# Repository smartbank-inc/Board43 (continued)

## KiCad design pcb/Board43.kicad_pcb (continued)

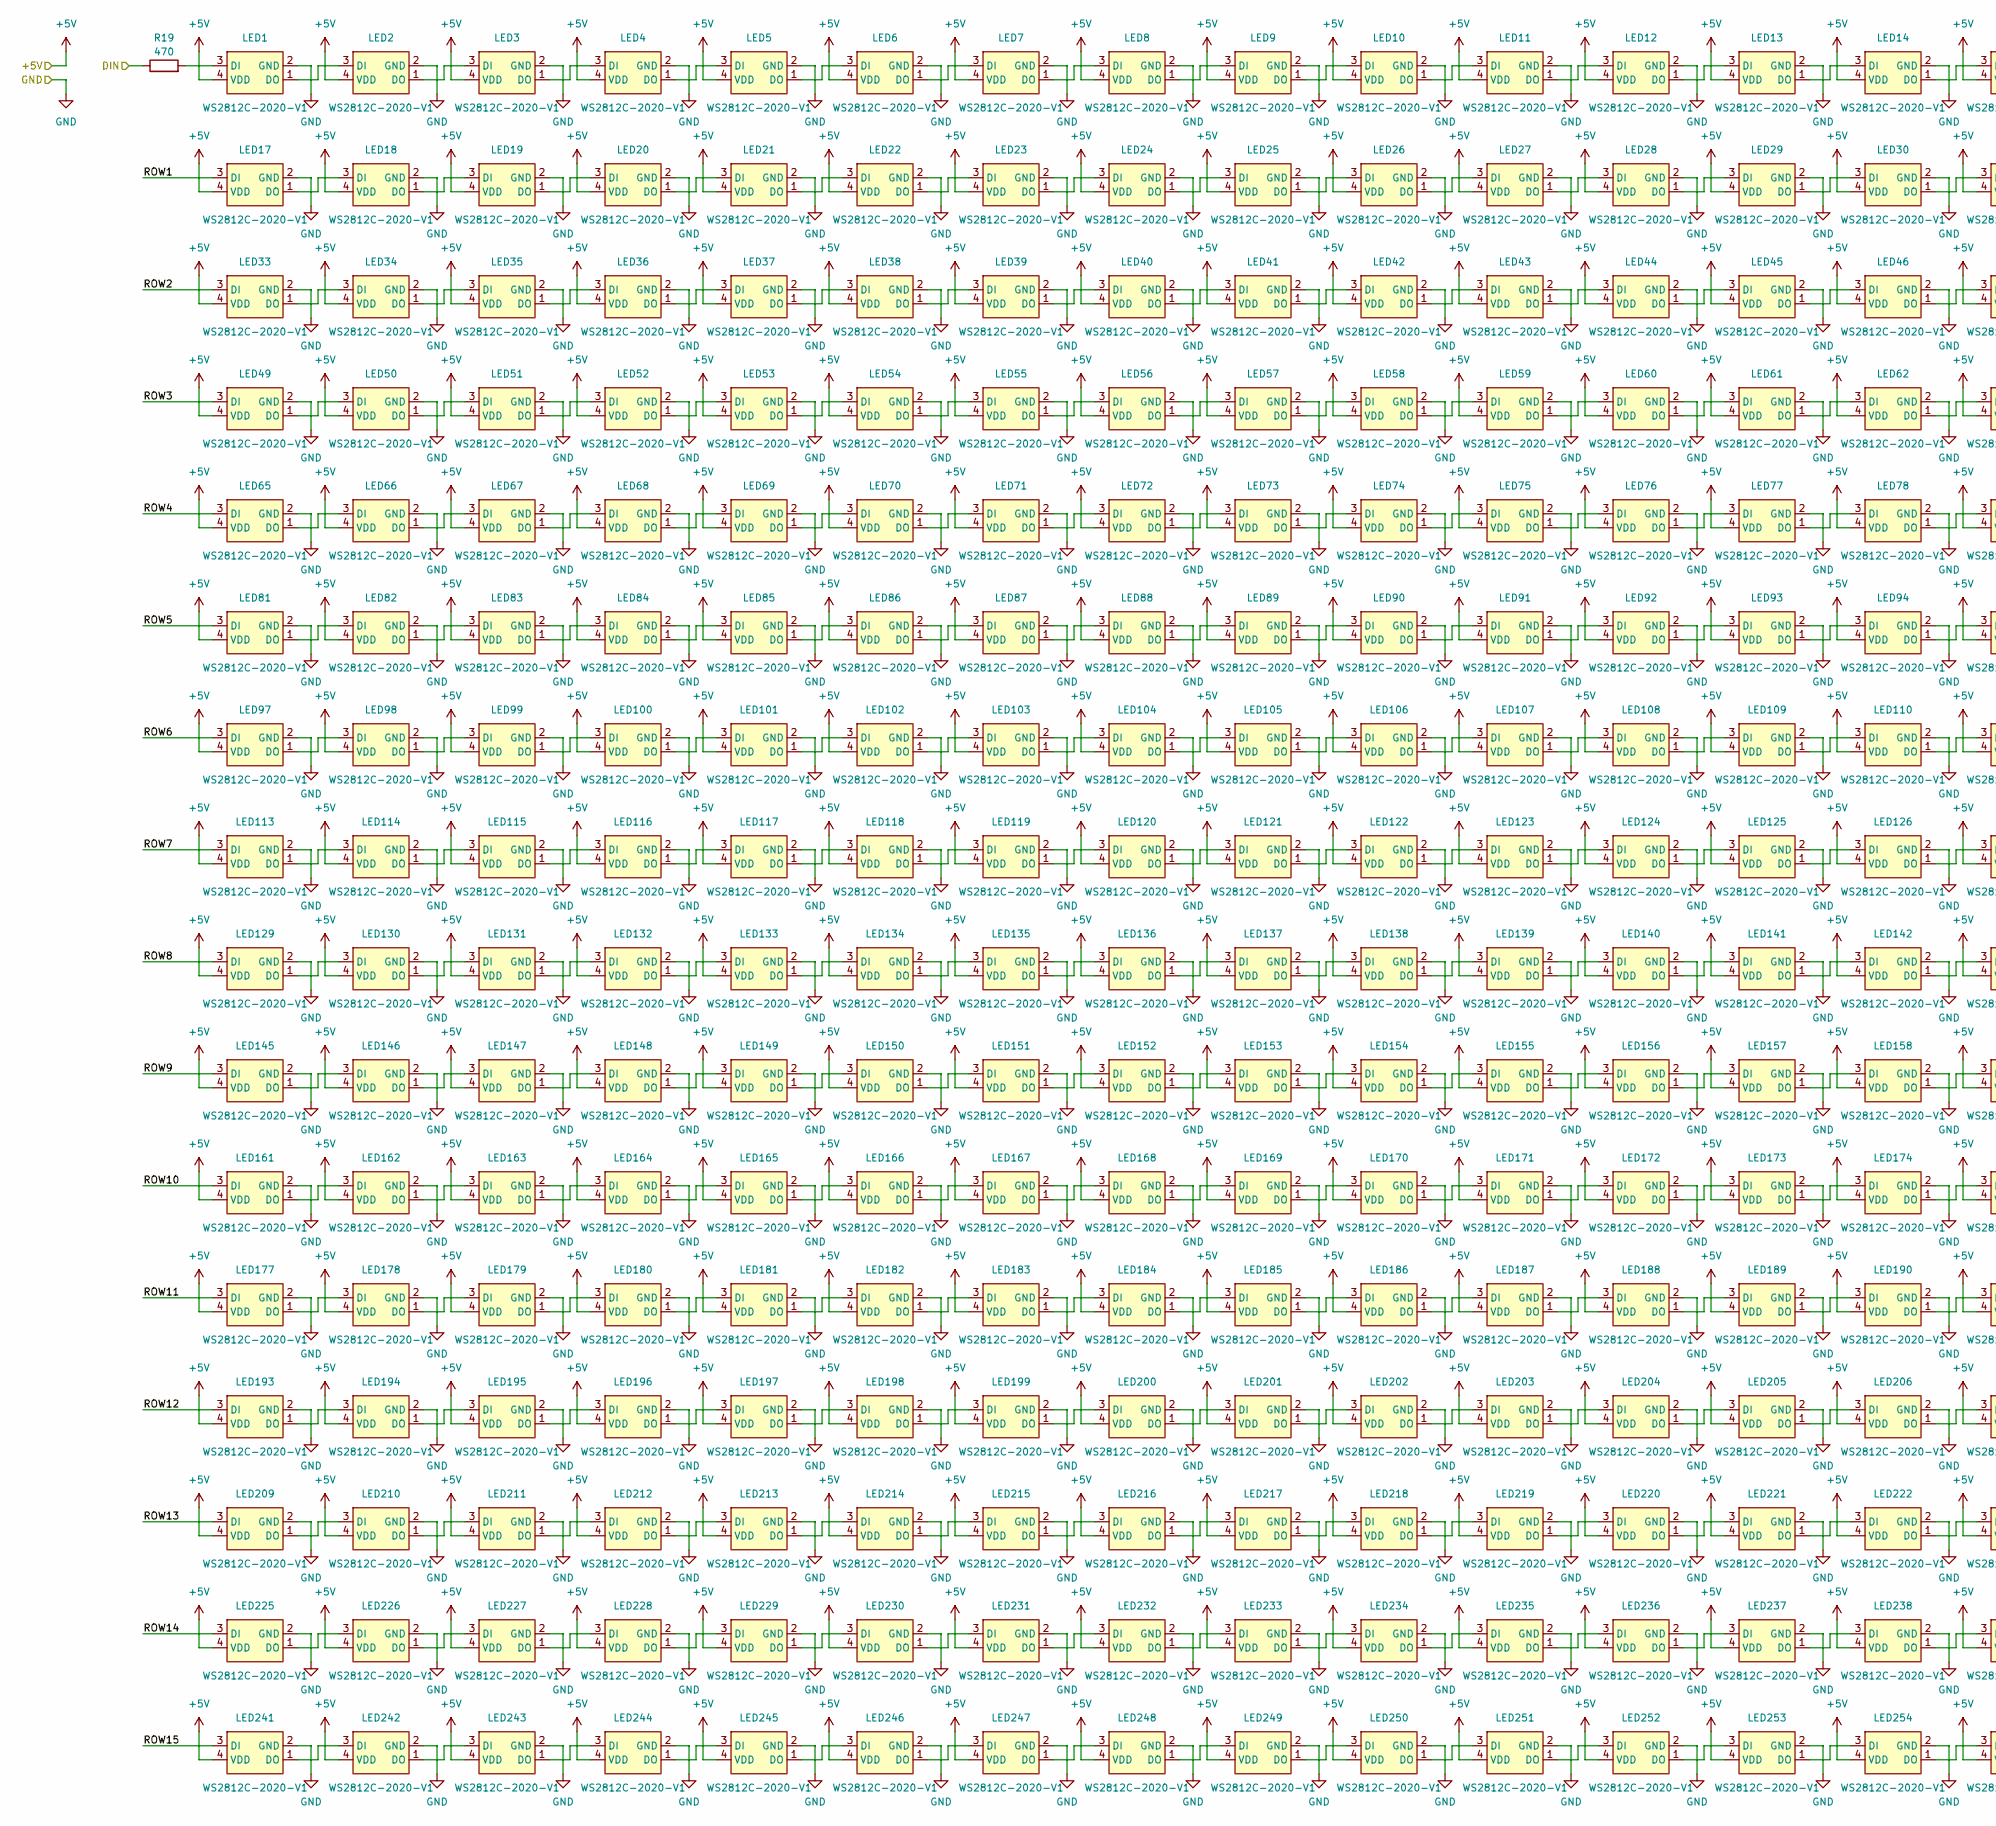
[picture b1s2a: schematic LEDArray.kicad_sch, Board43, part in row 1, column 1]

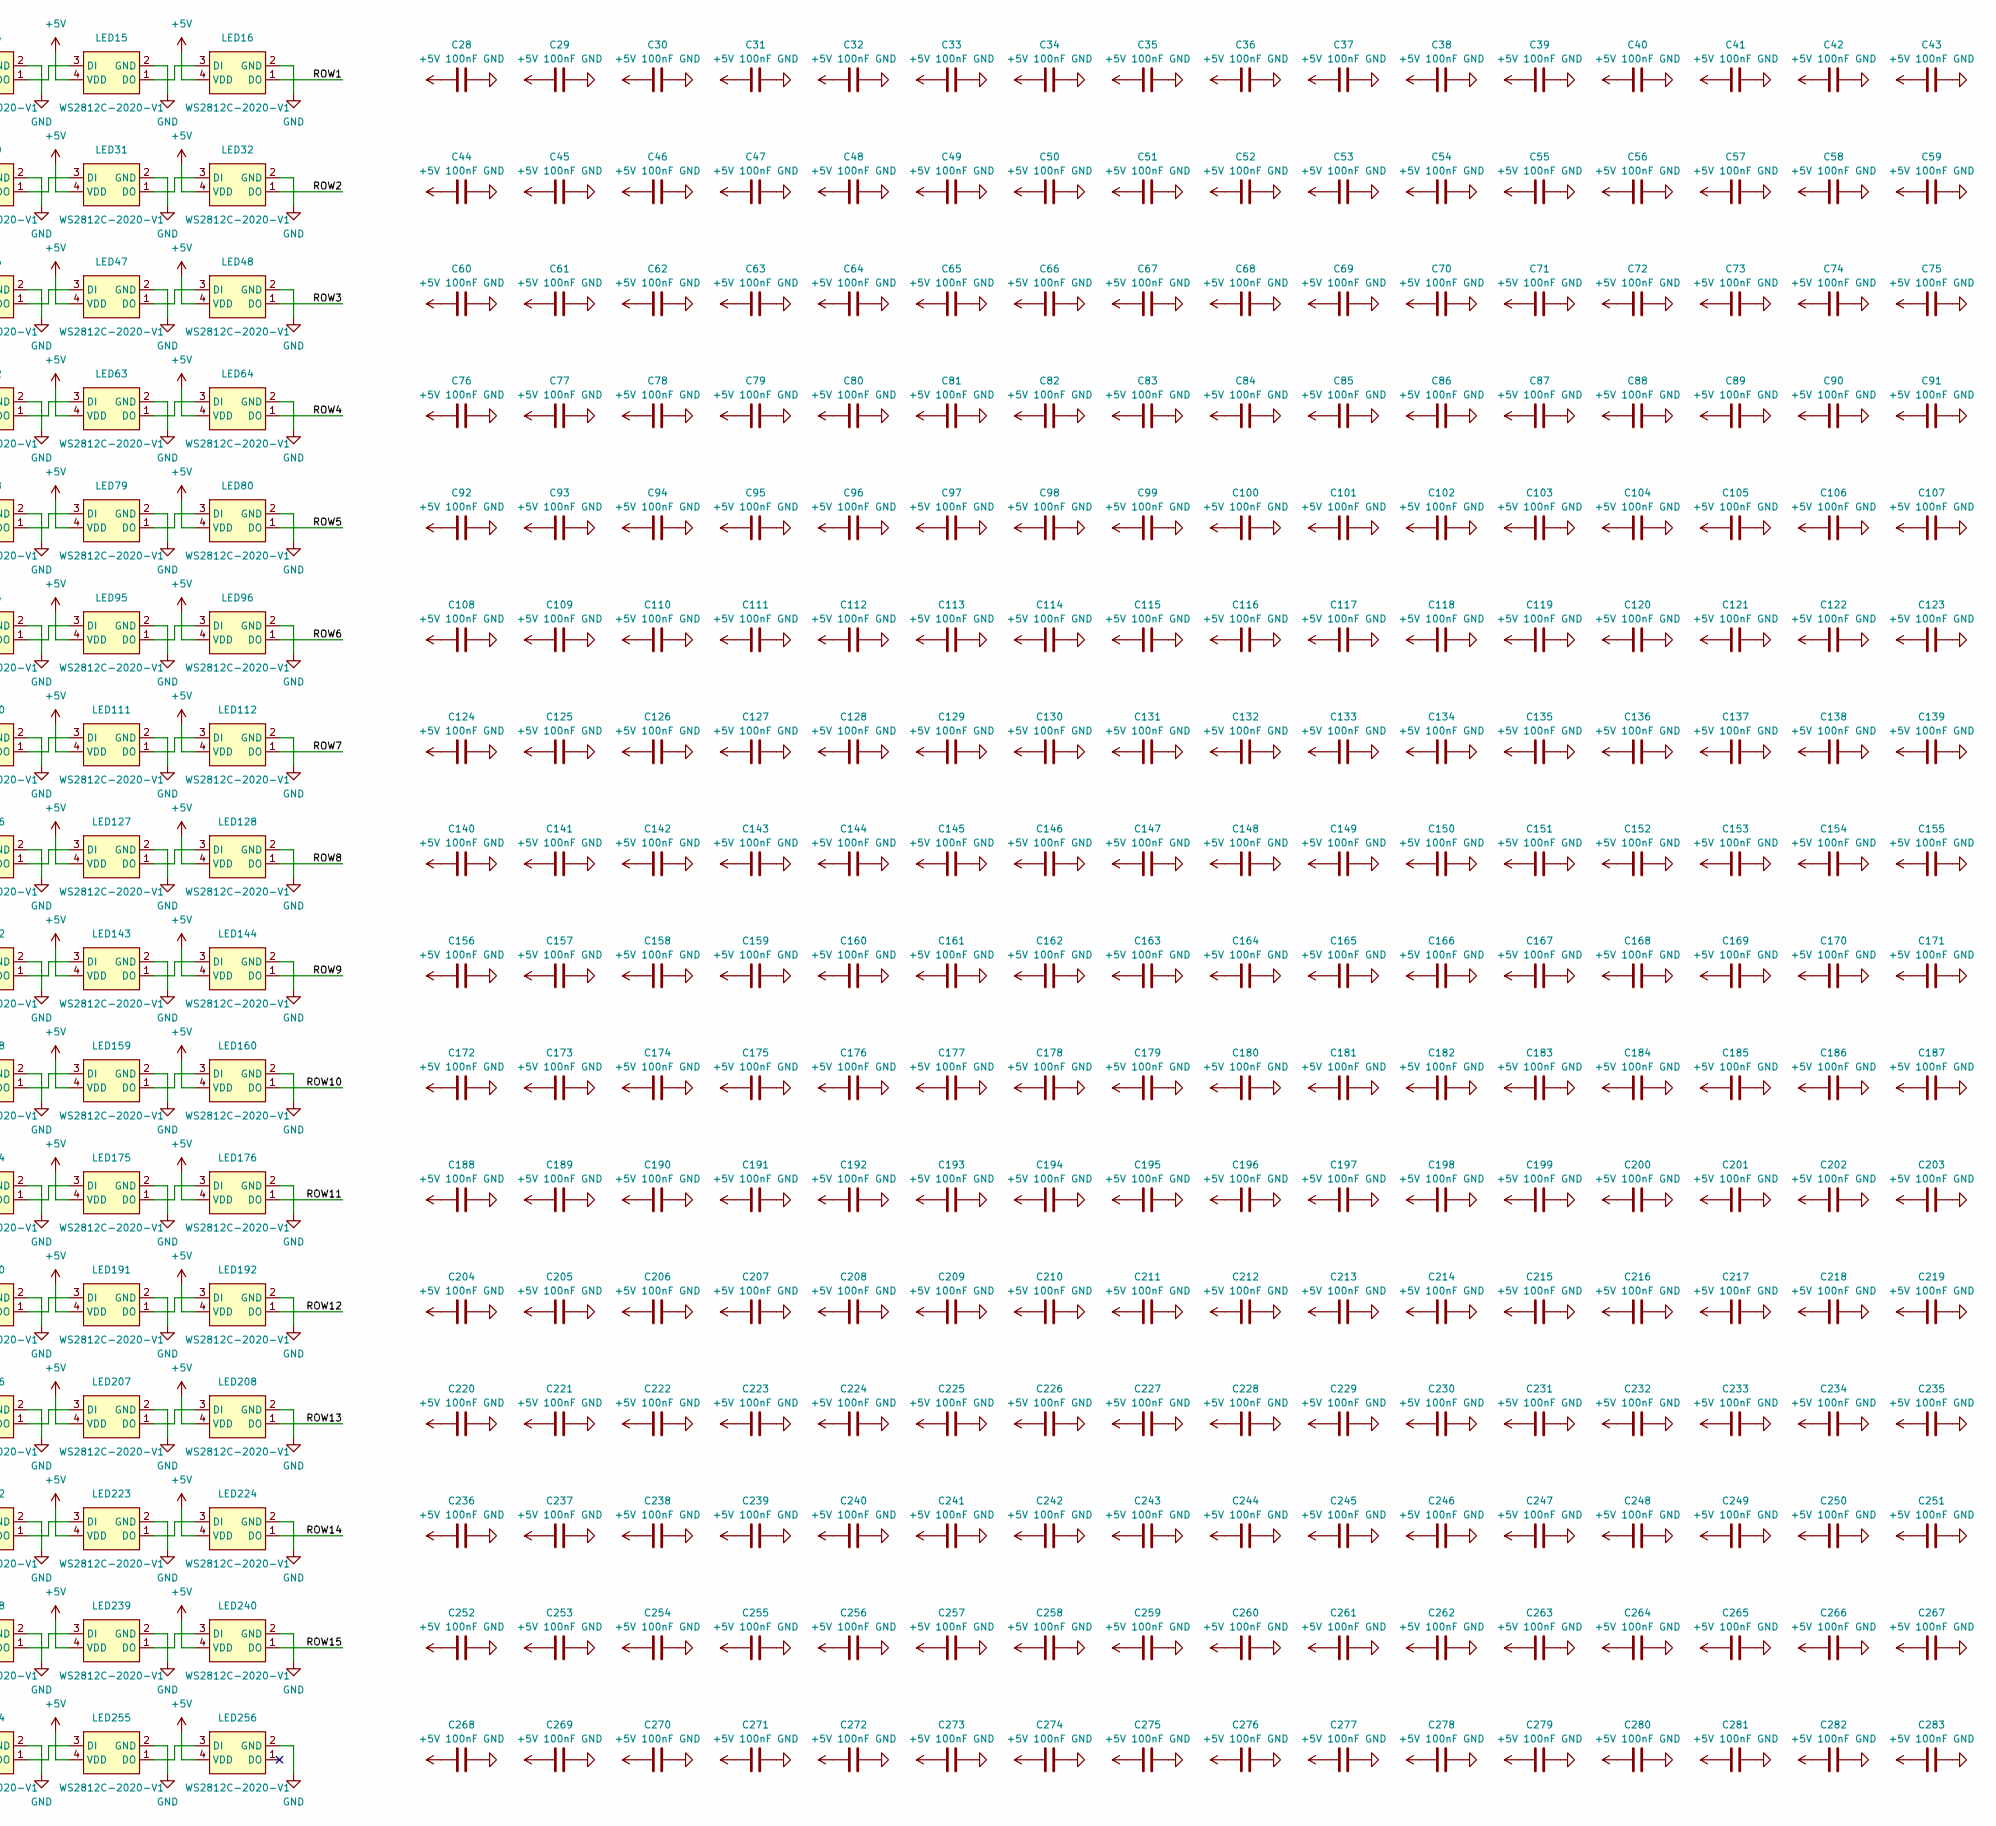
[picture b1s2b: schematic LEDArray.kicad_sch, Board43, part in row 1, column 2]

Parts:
C28, C29, C30, C31, C32, C33, C34, C35, C36, C37, C38, C39, C40, C41, C42, C43, C44, C45, C46, C47, C48, C49, C50, C51, C52, C53, C54, C55, C56, C57, C58, C59, C60, C61, C62, C63, C64, C65, C66, C67, C68, C69, C70, C71, C72, C73, C74, C75, C76, C77, C78, C79, C80, C81, C82, C83, C84, C85, C86, C87, C88, C89, C90, C91, C92, C93, C94, C95, C96, C97, C98, C99, C100, C101, C102, C103, C104, C105, C106, C107, C108, C109, C110, C111, C112, C113, C114, C115, C116, C117, C118, C119, C120, C121, C122, C123, C124, C125, C126, C127, C128, C129, C130, C131, C132, C133, C134, C135, C136, C137, C138, C139, C140, C141, C142, C143, C144, C145, C146, C147, C148, C149, C150, C151, C152, C153, C154, C155, C156, C157, C158, C159, C160, C161, C162, C163, C164, C165, C166, C167, C168, C169, C170, C171, C172, C173, C174, C175, C176, C177, C178, C179, C180, C181, C182, C183, C184, C185, C186, C187, C188, C189, C190, C191, C192, C193, C194, C195, C196, C197, C198, C199, C200, C201, C202, C203, C204, C205, C206, C207, C208, C209, C210, C211, C212, C213, C214, C215, C216, C217, C218, C219, C220, C221, C222, C223, C224, C225, C226, C227, C228, C229, C230, C231, C232, C233, C234, C235, C236, C237, C238, C239, C240, C241, C242, C243, C244, C245, C246, C247, C248, C249, C250, C251, C252, C253, C254, C255, C256, C257, C258, C259, C260, C261, C262, C263, C264, C265, C266, C267, C268, C269, C270, C271, C272, C273, C274, C275, C276, C277, C278, C279, C280, C281, C282, C283: 100nF; C_0201_0603Metric; LCSC C668346
LED1, LED2, LED3, LED4, LED5, LED6, LED7, LED8, LED9, LED10, LED11, LED12, LED13, LED14, LED15, LED16, LED17, LED18, LED19, LED20, LED21, LED22, LED23, LED24, LED25, LED26, LED27, LED28, LED29, LED30, LED31, LED32, LED33, LED34, LED35, LED36, LED37, LED38, LED39, LED40, LED41, LED42, LED43, LED44, LED45, LED46, LED47, LED48, LED49, LED50, LED51, LED52, LED53, LED54, LED55, LED56, LED57, LED58, LED59, LED60, LED61, LED62, LED63, LED64, LED65, LED66, LED67, LED68, LED69, LED70, LED71, LED72, LED73, LED74, LED75, LED76, LED77, LED78, LED79, LED80, LED81, LED82, LED83, LED84, LED85, LED86, LED87, LED88, LED89, LED90, LED91, LED92, LED93, LED94, LED95, LED96, LED97, LED98, LED99, LED100, LED101, LED102, LED103, LED104, LED105, LED106, LED107, LED108, LED109, LED110, LED111, LED112, LED113, LED114, LED115, LED116, LED117, LED118, LED119, LED120, LED121, LED122, LED123, LED124, LED125, LED126, LED127, LED128, LED129, LED130, LED131, LED132, LED133, LED134, LED135, LED136, LED137, LED138, LED139, LED140, LED141, LED142, LED143, LED144, LED145, LED146, LED147, LED148, LED149, LED150, LED151, LED152, LED153, LED154, LED155, LED156, LED157, LED158, LED159, LED160, LED161, LED162, LED163, LED164, LED165, LED166, LED167, LED168, LED169, LED170, LED171, LED172, LED173, LED174, LED175, LED176, LED177, LED178, LED179, LED180, LED181, LED182, LED183, LED184, LED185, LED186, LED187, LED188, LED189, LED190, LED191, LED192, LED193, LED194, LED195, LED196, LED197, LED198, LED199, LED200, LED201, LED202, LED203, LED204, LED205, LED206, LED207, LED208, LED209, LED210, LED211, LED212, LED213, LED214, LED215, LED216, LED217, LED218, LED219, LED220, LED221, LED222, LED223, LED224, LED225, LED226, LED227, LED228, LED229, LED230, LED231, LED232, LED233, LED234, LED235, LED236, LED237, LED238, LED239, LED240, LED241, LED242, LED243, LED244, LED245, LED246, LED247, LED248, LED249, LED250, LED251, LED252, LED253, LED254, LED255, LED256: WS2812C-2020-V1; LCSC C2976072
R19: 470; R_0201_0603Metric; LCSC C473464

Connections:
+5V: C28.1, C29.1, C30.1, C31.1, C32.1, C33.1, C34.1, C35.1, C36.1, C37.1, C38.1, C39.1, C40.1, C41.1, C42.1, C43.1, C44.1, C45.1, C46.1, C47.1, C48.1, C49.1, C50.1, C51.1, C52.1, C53.1, C54.1, C55.1, C56.1, C57.1, C58.1, C59.1, C60.1, C61.1, C62.1, C63.1, C64.1, C65.1, C66.1, C67.1, C68.1, C69.1, C70.1, C71.1, C72.1, C73.1, C74.1, C75.1, C76.1, C77.1, C78.1, C79.1, C80.1, C81.1, C82.1, C83.1, C84.1, C85.1, C86.1, C87.1, C88.1, C89.1, C90.1, C91.1, C92.1, C93.1, C94.1, C95.1, C96.1, C97.1, C98.1, C99.1, C100.1, C101.1, C102.1, C103.1, C104.1, C105.1, C106.1, C107.1, C108.1, C109.1, C110.1, C111.1, C112.1, C113.1, C114.1, C115.1, C116.1, C117.1, C118.1, C119.1, C120.1, C121.1, C122.1, C123.1, C124.1, C125.1, C126.1, C127.1, C128.1, C129.1, C130.1, C131.1, C132.1, C133.1, C134.1, C135.1, C136.1, C137.1, C138.1, C139.1, C140.1, C141.1, C142.1, C143.1, C144.1, C145.1, C146.1, C147.1, C148.1, C149.1, C150.1, C151.1, C152.1, C153.1, C154.1, C155.1, C156.1, C157.1, C158.1, C159.1, C160.1, C161.1, C162.1, C163.1, C164.1, C165.1, C166.1, C167.1, C168.1, C169.1, C170.1, C171.1, C172.1, C173.1, C174.1, C175.1, C176.1, C177.1, C178.1, C179.1, C180.1, C181.1, C182.1, C183.1, C184.1, C185.1, C186.1, C187.1, C188.1, C189.1, C190.1, C191.1, C192.1, C193.1, C194.1, C195.1, C196.1, C197.1, C198.1, C199.1, C200.1, C201.1, C202.1, C203.1, C204.1, C205.1, C206.1, C207.1, C208.1, C209.1, C210.1, C211.1, C212.1, C213.1, C214.1, C215.1, C216.1, C217.1, C218.1, C219.1, C220.1, C221.1, C222.1, C223.1, C224.1, C225.1, C226.1, C227.1, C228.1, C229.1, C230.1, C231.1, C232.1, C233.1, C234.1, C235.1, C236.1, C237.1, C238.1, C239.1, C240.1, C241.1, C242.1, C243.1, C244.1, C245.1, C246.1, C247.1, C248.1, C249.1, C250.1, C251.1, C252.1, C253.1, C254.1, C255.1, C256.1, C257.1, C258.1, C259.1, C260.1, C261.1, C262.1, C263.1, C264.1, C265.1, C266.1, C267.1, C268.1, C269.1, C270.1, C271.1, C272.1, C273.1, C274.1, C275.1, C276.1, C277.1, C278.1, C279.1, C280.1, C281.1, C282.1, C283.1, LED1.4 (VDD), LED2.4 (VDD), LED3.4 (VDD), LED4.4 (VDD), LED5.4 (VDD), LED6.4 (VDD), LED7.4 (VDD), LED8.4 (VDD), LED9.4 (VDD), LED10.4 (VDD), LED11.4 (VDD), LED12.4 (VDD), LED13.4 (VDD), LED14.4 (VDD), LED15.4 (VDD), LED16.4 (VDD), LED17.4 (VDD), LED18.4 (VDD), LED19.4 (VDD), LED20.4 (VDD), LED21.4 (VDD), LED22.4 (VDD), LED23.4 (VDD), LED24.4 (VDD), LED25.4 (VDD), LED26.4 (VDD), LED27.4 (VDD), LED28.4 (VDD), LED29.4 (VDD), LED30.4 (VDD), LED31.4 (VDD), LED32.4 (VDD), LED33.4 (VDD), LED34.4 (VDD), LED35.4 (VDD), LED36.4 (VDD), LED37.4 (VDD), LED38.4 (VDD), LED39.4 (VDD), LED40.4 (VDD), LED41.4 (VDD), LED42.4 (VDD), LED43.4 (VDD), LED44.4 (VDD), LED45.4 (VDD), LED46.4 (VDD), LED47.4 (VDD), LED48.4 (VDD), LED49.4 (VDD), LED50.4 (VDD), LED51.4 (VDD), LED52.4 (VDD), LED53.4 (VDD), LED54.4 (VDD), LED55.4 (VDD), LED56.4 (VDD), LED57.4 (VDD), LED58.4 (VDD), LED59.4 (VDD), LED60.4 (VDD), LED61.4 (VDD), LED62.4 (VDD), LED63.4 (VDD), LED64.4 (VDD), LED65.4 (VDD), LED66.4 (VDD), LED67.4 (VDD), LED68.4 (VDD), LED69.4 (VDD), LED70.4 (VDD), LED71.4 (VDD), LED72.4 (VDD), LED73.4 (VDD), LED74.4 (VDD), LED75.4 (VDD), LED76.4 (VDD), LED77.4 (VDD), LED78.4 (VDD), LED79.4 (VDD), LED80.4 (VDD), LED81.4 (VDD), LED82.4 (VDD), LED83.4 (VDD), LED84.4 (VDD), LED85.4 (VDD), LED86.4 (VDD), LED87.4 (VDD), LED88.4 (VDD), LED89.4 (VDD), LED90.4 (VDD), LED91.4 (VDD), LED92.4 (VDD), LED93.4 (VDD), LED94.4 (VDD), LED95.4 (VDD), LED96.4 (VDD), LED97.4 (VDD), LED98.4 (VDD), LED99.4 (VDD), LED100.4 (VDD), LED101.4 (VDD), LED102.4 (VDD), LED103.4 (VDD), LED104.4 (VDD), LED105.4 (VDD), LED106.4 (VDD), LED107.4 (VDD), LED108.4 (VDD), LED109.4 (VDD), LED110.4 (VDD), LED111.4 (VDD), LED112.4 (VDD), LED113.4 (VDD), LED114.4 (VDD), LED115.4 (VDD), LED116.4 (VDD), LED117.4 (VDD), LED118.4 (VDD), LED119.4 (VDD), LED120.4 (VDD), LED121.4 (VDD), LED122.4 (VDD), LED123.4 (VDD), LED124.4 (VDD), LED125.4 (VDD), LED126.4 (VDD), LED127.4 (VDD), LED128.4 (VDD), LED129.4 (VDD), LED130.4 (VDD), LED131.4 (VDD), LED132.4 (VDD), LED133.4 (VDD), LED134.4 (VDD), LED135.4 (VDD), LED136.4 (VDD), LED137.4 (VDD), LED138.4 (VDD), LED139.4 (VDD), LED140.4 (VDD), LED141.4 (VDD), LED142.4 (VDD), LED143.4 (VDD), LED144.4 (VDD), LED145.4 (VDD), LED146.4 (VDD), LED147.4 (VDD), LED148.4 (VDD), LED149.4 (VDD), LED150.4 (VDD), LED151.4 (VDD), LED152.4 (VDD), LED153.4 (VDD), LED154.4 (VDD), LED155.4 (VDD), LED156.4 (VDD), LED157.4 (VDD), LED158.4 (VDD), LED159.4 (VDD), LED160.4 (VDD), LED161.4 (VDD), LED162.4 (VDD), LED163.4 (VDD), LED164.4 (VDD), LED165.4 (VDD), LED166.4 (VDD), LED167.4 (VDD), LED168.4 (VDD), LED169.4 (VDD), LED170.4 (VDD), LED171.4 (VDD), LED172.4 (VDD), LED173.4 (VDD), LED174.4 (VDD), LED175.4 (VDD), LED176.4 (VDD), LED177.4 (VDD), LED178.4 (VDD), LED179.4 (VDD), LED180.4 (VDD), LED181.4 (VDD), LED182.4 (VDD), LED183.4 (VDD), LED184.4 (VDD), LED185.4 (VDD), LED186.4 (VDD), LED187.4 (VDD), LED188.4 (VDD), LED189.4 (VDD), LED190.4 (VDD), LED191.4 (VDD), LED192.4 (VDD), LED193.4 (VDD), LED194.4 (VDD), LED195.4 (VDD), LED196.4 (VDD), LED197.4 (VDD), LED198.4 (VDD), LED199.4 (VDD), LED200.4 (VDD), LED201.4 (VDD), LED202.4 (VDD), LED203.4 (VDD), LED204.4 (VDD), LED205.4 (VDD), LED206.4 (VDD), LED207.4 (VDD), LED208.4 (VDD), LED209.4 (VDD), LED210.4 (VDD), LED211.4 (VDD), LED212.4 (VDD), LED213.4 (VDD), LED214.4 (VDD), LED215.4 (VDD), LED216.4 (VDD), LED217.4 (VDD), LED218.4 (VDD), LED219.4 (VDD), LED220.4 (VDD), LED221.4 (VDD), LED222.4 (VDD), LED223.4 (VDD), LED224.4 (VDD), LED225.4 (VDD), LED226.4 (VDD), LED227.4 (VDD), LED228.4 (VDD), LED229.4 (VDD), LED230.4 (VDD), LED231.4 (VDD), LED232.4 (VDD), LED233.4 (VDD), LED234.4 (VDD), LED235.4 (VDD), LED236.4 (VDD), LED237.4 (VDD), LED238.4 (VDD), LED239.4 (VDD), LED240.4 (VDD), LED241.4 (VDD), LED242.4 (VDD), LED243.4 (VDD), LED244.4 (VDD), LED245.4 (VDD), LED246.4 (VDD), LED247.4 (VDD), LED248.4 (VDD), LED249.4 (VDD), LED250.4 (VDD), LED251.4 (VDD), LED252.4 (VDD), LED253.4 (VDD), LED254.4 (VDD), LED255.4 (VDD), LED256.4 (VDD); also elsewhere on the board
/LED OUT: R19.1; also elsewhere on the board
/LEDArray/ROW1: LED16.1 (DO), LED17.3 (DI)
/LEDArray/ROW2: LED32.1 (DO), LED33.3 (DI)
/LEDArray/ROW3: LED48.1 (DO), LED49.3 (DI)
/LEDArray/ROW4: LED64.1 (DO), LED65.3 (DI)
/LEDArray/ROW5: LED80.1 (DO), LED81.3 (DI)
/LEDArray/ROW6: LED96.1 (DO), LED97.3 (DI)
/LEDArray/ROW7: LED112.1 (DO), LED113.3 (DI)
/LEDArray/ROW8: LED128.1 (DO), LED129.3 (DI)
/LEDArray/ROW9: LED144.1 (DO), LED145.3 (DI)
/LEDArray/ROW10: LED160.1 (DO), LED161.3 (DI)
/LEDArray/ROW11: LED176.1 (DO), LED177.3 (DI)
/LEDArray/ROW12: LED192.1 (DO), LED193.3 (DI)
/LEDArray/ROW13: LED208.1 (DO), LED209.3 (DI)
/LEDArray/ROW14: LED224.1 (DO), LED225.3 (DI)
/LEDArray/ROW15: LED240.1 (DO), LED241.3 (DI)
GND: C28.2, C29.2, C30.2, C31.2, C32.2, C33.2, C34.2, C35.2, C36.2, C37.2, C38.2, C39.2, C40.2, C41.2, C42.2, C43.2, C44.2, C45.2, C46.2, C47.2, C48.2, C49.2, C50.2, C51.2, C52.2, C53.2, C54.2, C55.2, C56.2, C57.2, C58.2, C59.2, C60.2, C61.2, C62.2, C63.2, C64.2, C65.2, C66.2, C67.2, C68.2, C69.2, C70.2, C71.2, C72.2, C73.2, C74.2, C75.2, C76.2, C77.2, C78.2, C79.2, C80.2, C81.2, C82.2, C83.2, C84.2, C85.2, C86.2, C87.2, C88.2, C89.2, C90.2, C91.2, C92.2, C93.2, C94.2, C95.2, C96.2, C97.2, C98.2, C99.2, C100.2, C101.2, C102.2, C103.2, C104.2, C105.2, C106.2, C107.2, C108.2, C109.2, C110.2, C111.2, C112.2, C113.2, C114.2, C115.2, C116.2, C117.2, C118.2, C119.2, C120.2, C121.2, C122.2, C123.2, C124.2, C125.2, C126.2, C127.2, C128.2, C129.2, C130.2, C131.2, C132.2, C133.2, C134.2, C135.2, C136.2, C137.2, C138.2, C139.2, C140.2, C141.2, C142.2, C143.2, C144.2, C145.2, C146.2, C147.2, C148.2, C149.2, C150.2, C151.2, C152.2, C153.2, C154.2, C155.2, C156.2, C157.2, C158.2, C159.2, C160.2, C161.2, C162.2, C163.2, C164.2, C165.2, C166.2, C167.2, C168.2, C169.2, C170.2, C171.2, C172.2, C173.2, C174.2, C175.2, C176.2, C177.2, C178.2, C179.2, C180.2, C181.2, C182.2, C183.2, C184.2, C185.2, C186.2, C187.2, C188.2, C189.2, C190.2, C191.2, C192.2, C193.2, C194.2, C195.2, C196.2, C197.2, C198.2, C199.2, C200.2, C201.2, C202.2, C203.2, C204.2, C205.2, C206.2, C207.2, C208.2, C209.2, C210.2, C211.2, C212.2, C213.2, C214.2, C215.2, C216.2, C217.2, C218.2, C219.2, C220.2, C221.2, C222.2, C223.2, C224.2, C225.2, C226.2, C227.2, C228.2, C229.2, C230.2, C231.2, C232.2, C233.2, C234.2, C235.2, C236.2, C237.2, C238.2, C239.2, C240.2, C241.2, C242.2, C243.2, C244.2, C245.2, C246.2, C247.2, C248.2, C249.2, C250.2, C251.2, C252.2, C253.2, C254.2, C255.2, C256.2, C257.2, C258.2, C259.2, C260.2, C261.2, C262.2, C263.2, C264.2, C265.2, C266.2, C267.2, C268.2, C269.2, C270.2, C271.2, C272.2, C273.2, C274.2, C275.2, C276.2, C277.2, C278.2, C279.2, C280.2, C281.2, C282.2, C283.2, LED1.2 (GND), LED2.2 (GND), LED3.2 (GND), LED4.2 (GND), LED5.2 (GND), LED6.2 (GND), LED7.2 (GND), LED8.2 (GND), LED9.2 (GND), LED10.2 (GND), LED11.2 (GND), LED12.2 (GND), LED13.2 (GND), LED14.2 (GND), LED15.2 (GND), LED16.2 (GND), LED17.2 (GND), LED18.2 (GND), LED19.2 (GND), LED20.2 (GND), LED21.2 (GND), LED22.2 (GND), LED23.2 (GND), LED24.2 (GND), LED25.2 (GND), LED26.2 (GND), LED27.2 (GND), LED28.2 (GND), LED29.2 (GND), LED30.2 (GND), LED31.2 (GND), LED32.2 (GND), LED33.2 (GND), LED34.2 (GND), LED35.2 (GND), LED36.2 (GND), LED37.2 (GND), LED38.2 (GND), LED39.2 (GND), LED40.2 (GND), LED41.2 (GND), LED42.2 (GND), LED43.2 (GND), LED44.2 (GND), LED45.2 (GND), LED46.2 (GND), LED47.2 (GND), LED48.2 (GND), LED49.2 (GND), LED50.2 (GND), LED51.2 (GND), LED52.2 (GND), LED53.2 (GND), LED54.2 (GND), LED55.2 (GND), LED56.2 (GND), LED57.2 (GND), LED58.2 (GND), LED59.2 (GND), LED60.2 (GND), LED61.2 (GND), LED62.2 (GND), LED63.2 (GND), LED64.2 (GND), LED65.2 (GND), LED66.2 (GND), LED67.2 (GND), LED68.2 (GND), LED69.2 (GND), LED70.2 (GND), LED71.2 (GND), LED72.2 (GND), LED73.2 (GND), LED74.2 (GND), LED75.2 (GND), LED76.2 (GND), LED77.2 (GND), LED78.2 (GND), LED79.2 (GND), LED80.2 (GND), LED81.2 (GND), LED82.2 (GND), LED83.2 (GND), LED84.2 (GND), LED85.2 (GND), LED86.2 (GND), LED87.2 (GND), LED88.2 (GND), LED89.2 (GND), LED90.2 (GND), LED91.2 (GND), LED92.2 (GND), LED93.2 (GND), LED94.2 (GND), LED95.2 (GND), LED96.2 (GND), LED97.2 (GND), LED98.2 (GND), LED99.2 (GND), LED100.2 (GND), LED101.2 (GND), LED102.2 (GND), LED103.2 (GND), LED104.2 (GND), LED105.2 (GND), LED106.2 (GND), LED107.2 (GND), LED108.2 (GND), LED109.2 (GND), LED110.2 (GND), LED111.2 (GND), LED112.2 (GND), LED113.2 (GND), LED114.2 (GND), LED115.2 (GND), LED116.2 (GND), LED117.2 (GND), LED118.2 (GND), LED119.2 (GND), LED120.2 (GND), LED121.2 (GND), LED122.2 (GND), LED123.2 (GND), LED124.2 (GND), LED125.2 (GND), LED126.2 (GND), LED127.2 (GND), LED128.2 (GND), LED129.2 (GND), LED130.2 (GND), LED131.2 (GND), LED132.2 (GND), LED133.2 (GND), LED134.2 (GND), LED135.2 (GND), LED136.2 (GND), LED137.2 (GND), LED138.2 (GND), LED139.2 (GND), LED140.2 (GND), LED141.2 (GND), LED142.2 (GND), LED143.2 (GND), LED144.2 (GND), LED145.2 (GND), LED146.2 (GND), LED147.2 (GND), LED148.2 (GND), LED149.2 (GND), LED150.2 (GND), LED151.2 (GND), LED152.2 (GND), LED153.2 (GND), LED154.2 (GND), LED155.2 (GND), LED156.2 (GND), LED157.2 (GND), LED158.2 (GND), LED159.2 (GND), LED160.2 (GND), LED161.2 (GND), LED162.2 (GND), LED163.2 (GND), LED164.2 (GND), LED165.2 (GND), LED166.2 (GND), LED167.2 (GND), LED168.2 (GND), LED169.2 (GND), LED170.2 (GND), LED171.2 (GND), LED172.2 (GND), LED173.2 (GND), LED174.2 (GND), LED175.2 (GND), LED176.2 (GND), LED177.2 (GND), LED178.2 (GND), LED179.2 (GND), LED180.2 (GND), LED181.2 (GND), LED182.2 (GND), LED183.2 (GND), LED184.2 (GND), LED185.2 (GND), LED186.2 (GND), LED187.2 (GND), LED188.2 (GND), LED189.2 (GND), LED190.2 (GND), LED191.2 (GND), LED192.2 (GND), LED193.2 (GND), LED194.2 (GND), LED195.2 (GND), LED196.2 (GND), LED197.2 (GND), LED198.2 (GND), LED199.2 (GND), LED200.2 (GND), LED201.2 (GND), LED202.2 (GND), LED203.2 (GND), LED204.2 (GND), LED205.2 (GND), LED206.2 (GND), LED207.2 (GND), LED208.2 (GND), LED209.2 (GND), LED210.2 (GND), LED211.2 (GND), LED212.2 (GND), LED213.2 (GND), LED214.2 (GND), LED215.2 (GND), LED216.2 (GND), LED217.2 (GND), LED218.2 (GND), LED219.2 (GND), LED220.2 (GND), LED221.2 (GND), LED222.2 (GND), LED223.2 (GND), LED224.2 (GND), LED225.2 (GND), LED226.2 (GND), LED227.2 (GND), LED228.2 (GND), LED229.2 (GND), LED230.2 (GND), LED231.2 (GND), LED232.2 (GND), LED233.2 (GND), LED234.2 (GND), LED235.2 (GND), LED236.2 (GND), LED237.2 (GND), LED238.2 (GND), LED239.2 (GND), LED240.2 (GND), LED241.2 (GND), LED242.2 (GND), LED243.2 (GND), LED244.2 (GND), LED245.2 (GND), LED246.2 (GND), LED247.2 (GND), LED248.2 (GND), LED249.2 (GND), LED250.2 (GND), LED251.2 (GND), LED252.2 (GND), LED253.2 (GND), LED254.2 (GND), LED255.2 (GND), LED256.2 (GND); also elsewhere on the board
unnamed: LED1.3 (DI), R19.2
unnamed: LED1.1 (DO), LED2.3 (DI)
unnamed: LED2.1 (DO), LED3.3 (DI)
unnamed: LED3.1 (DO), LED4.3 (DI)
unnamed: LED4.1 (DO), LED5.3 (DI)
unnamed: LED5.1 (DO), LED6.3 (DI)
unnamed: LED6.1 (DO), LED7.3 (DI)
unnamed: LED7.1 (DO), LED8.3 (DI)
unnamed: LED8.1 (DO), LED9.3 (DI)
unnamed: LED9.1 (DO), LED10.3 (DI)
unnamed: LED10.1 (DO), LED11.3 (DI)
unnamed: LED11.1 (DO), LED12.3 (DI)
unnamed: LED12.1 (DO), LED13.3 (DI)
unnamed: LED13.1 (DO), LED14.3 (DI)
unnamed: LED14.1 (DO), LED15.3 (DI)
unnamed: LED15.1 (DO), LED16.3 (DI)
unnamed: LED17.1 (DO), LED18.3 (DI)
unnamed: LED18.1 (DO), LED19.3 (DI)
unnamed: LED19.1 (DO), LED20.3 (DI)
unnamed: LED20.1 (DO), LED21.3 (DI)
unnamed: LED21.1 (DO), LED22.3 (DI)
unnamed: LED22.1 (DO), LED23.3 (DI)
unnamed: LED23.1 (DO), LED24.3 (DI)
unnamed: LED24.1 (DO), LED25.3 (DI)
unnamed: LED25.1 (DO), LED26.3 (DI)
unnamed: LED26.1 (DO), LED27.3 (DI)
unnamed: LED27.1 (DO), LED28.3 (DI)
unnamed: LED28.1 (DO), LED29.3 (DI)
unnamed: LED29.1 (DO), LED30.3 (DI)
unnamed: LED30.1 (DO), LED31.3 (DI)
unnamed: LED31.1 (DO), LED32.3 (DI)
unnamed: LED33.1 (DO), LED34.3 (DI)
unnamed: LED34.1 (DO), LED35.3 (DI)
unnamed: LED35.1 (DO), LED36.3 (DI)
unnamed: LED36.1 (DO), LED37.3 (DI)
unnamed: LED37.1 (DO), LED38.3 (DI)
unnamed: LED38.1 (DO), LED39.3 (DI)
unnamed: LED39.1 (DO), LED40.3 (DI)
unnamed: LED40.1 (DO), LED41.3 (DI)
unnamed: LED41.1 (DO), LED42.3 (DI)
unnamed: LED42.1 (DO), LED43.3 (DI)
unnamed: LED43.1 (DO), LED44.3 (DI)
unnamed: LED44.1 (DO), LED45.3 (DI)
unnamed: LED45.1 (DO), LED46.3 (DI)
unnamed: LED46.1 (DO), LED47.3 (DI)
unnamed: LED47.1 (DO), LED48.3 (DI)
unnamed: LED49.1 (DO), LED50.3 (DI)
unnamed: LED50.1 (DO), LED51.3 (DI)
unnamed: LED51.1 (DO), LED52.3 (DI)
unnamed: LED52.1 (DO), LED53.3 (DI)
unnamed: LED53.1 (DO), LED54.3 (DI)
unnamed: LED54.1 (DO), LED55.3 (DI)
unnamed: LED55.1 (DO), LED56.3 (DI)
unnamed: LED56.1 (DO), LED57.3 (DI)
unnamed: LED57.1 (DO), LED58.3 (DI)
unnamed: LED58.1 (DO), LED59.3 (DI)
unnamed: LED59.1 (DO), LED60.3 (DI)
unnamed: LED60.1 (DO), LED61.3 (DI)
unnamed: LED61.1 (DO), LED62.3 (DI)
unnamed: LED62.1 (DO), LED63.3 (DI)
unnamed: LED63.1 (DO), LED64.3 (DI)
unnamed: LED65.1 (DO), LED66.3 (DI)
unnamed: LED66.1 (DO), LED67.3 (DI)
unnamed: LED67.1 (DO), LED68.3 (DI)
unnamed: LED68.1 (DO), LED69.3 (DI)
unnamed: LED69.1 (DO), LED70.3 (DI)
unnamed: LED70.1 (DO), LED71.3 (DI)
unnamed: LED71.1 (DO), LED72.3 (DI)
unnamed: LED72.1 (DO), LED73.3 (DI)
unnamed: LED73.1 (DO), LED74.3 (DI)
unnamed: LED74.1 (DO), LED75.3 (DI)
unnamed: LED75.1 (DO), LED76.3 (DI)
unnamed: LED76.1 (DO), LED77.3 (DI)
unnamed: LED77.1 (DO), LED78.3 (DI)
unnamed: LED78.1 (DO), LED79.3 (DI)
unnamed: LED79.1 (DO), LED80.3 (DI)
unnamed: LED81.1 (DO), LED82.3 (DI)
unnamed: LED82.1 (DO), LED83.3 (DI)
unnamed: LED83.1 (DO), LED84.3 (DI)
unnamed: LED84.1 (DO), LED85.3 (DI)
unnamed: LED85.1 (DO), LED86.3 (DI)
unnamed: LED86.1 (DO), LED87.3 (DI)
unnamed: LED87.1 (DO), LED88.3 (DI)
unnamed: LED88.1 (DO), LED89.3 (DI)
unnamed: LED89.1 (DO), LED90.3 (DI)
unnamed: LED90.1 (DO), LED91.3 (DI)
unnamed: LED91.1 (DO), LED92.3 (DI)
unnamed: LED92.1 (DO), LED93.3 (DI)
unnamed: LED93.1 (DO), LED94.3 (DI)
unnamed: LED94.1 (DO), LED95.3 (DI)
unnamed: LED95.1 (DO), LED96.3 (DI)
unnamed: LED97.1 (DO), LED98.3 (DI)
unnamed: LED98.1 (DO), LED99.3 (DI)
unnamed: LED99.1 (DO), LED100.3 (DI)
unnamed: LED100.1 (DO), LED101.3 (DI)
unnamed: LED101.1 (DO), LED102.3 (DI)
unnamed: LED102.1 (DO), LED103.3 (DI)
unnamed: LED103.1 (DO), LED104.3 (DI)
unnamed: LED104.1 (DO), LED105.3 (DI)
unnamed: LED105.1 (DO), LED106.3 (DI)
unnamed: LED106.1 (DO), LED107.3 (DI)
unnamed: LED107.1 (DO), LED108.3 (DI)
unnamed: LED108.1 (DO), LED109.3 (DI)
unnamed: LED109.1 (DO), LED110.3 (DI)
unnamed: LED110.1 (DO), LED111.3 (DI)
unnamed: LED111.1 (DO), LED112.3 (DI)
unnamed: LED113.1 (DO), LED114.3 (DI)
unnamed: LED114.1 (DO), LED115.3 (DI)
unnamed: LED115.1 (DO), LED116.3 (DI)
unnamed: LED116.1 (DO), LED117.3 (DI)
unnamed: LED117.1 (DO), LED118.3 (DI)
unnamed: LED118.1 (DO), LED119.3 (DI)
unnamed: LED119.1 (DO), LED120.3 (DI)
unnamed: LED120.1 (DO), LED121.3 (DI)
unnamed: LED121.1 (DO), LED122.3 (DI)
unnamed: LED122.1 (DO), LED123.3 (DI)
unnamed: LED123.1 (DO), LED124.3 (DI)
unnamed: LED124.1 (DO), LED125.3 (DI)
unnamed: LED125.1 (DO), LED126.3 (DI)
unnamed: LED126.1 (DO), LED127.3 (DI)
unnamed: LED127.1 (DO), LED128.3 (DI)
unnamed: LED129.1 (DO), LED130.3 (DI)
unnamed: LED130.1 (DO), LED131.3 (DI)
unnamed: LED131.1 (DO), LED132.3 (DI)
unnamed: LED132.1 (DO), LED133.3 (DI)
unnamed: LED133.1 (DO), LED134.3 (DI)
unnamed: LED134.1 (DO), LED135.3 (DI)
unnamed: LED135.1 (DO), LED136.3 (DI)
unnamed: LED136.1 (DO), LED137.3 (DI)
unnamed: LED137.1 (DO), LED138.3 (DI)
unnamed: LED138.1 (DO), LED139.3 (DI)
unnamed: LED139.1 (DO), LED140.3 (DI)
unnamed: LED140.1 (DO), LED141.3 (DI)
unnamed: LED141.1 (DO), LED142.3 (DI)
unnamed: LED142.1 (DO), LED143.3 (DI)
unnamed: LED143.1 (DO), LED144.3 (DI)
unnamed: LED145.1 (DO), LED146.3 (DI)
unnamed: LED146.1 (DO), LED147.3 (DI)
unnamed: LED147.1 (DO), LED148.3 (DI)
unnamed: LED148.1 (DO), LED149.3 (DI)
unnamed: LED149.1 (DO), LED150.3 (DI)
unnamed: LED150.1 (DO), LED151.3 (DI)
unnamed: LED151.1 (DO), LED152.3 (DI)
unnamed: LED152.1 (DO), LED153.3 (DI)
unnamed: LED153.1 (DO), LED154.3 (DI)
unnamed: LED154.1 (DO), LED155.3 (DI)
unnamed: LED155.1 (DO), LED156.3 (DI)
unnamed: LED156.1 (DO), LED157.3 (DI)
unnamed: LED157.1 (DO), LED158.3 (DI)
unnamed: LED158.1 (DO), LED159.3 (DI)
unnamed: LED159.1 (DO), LED160.3 (DI)
unnamed: LED161.1 (DO), LED162.3 (DI)
unnamed: LED162.1 (DO), LED163.3 (DI)
unnamed: LED163.1 (DO), LED164.3 (DI)
unnamed: LED164.1 (DO), LED165.3 (DI)
unnamed: LED165.1 (DO), LED166.3 (DI)
unnamed: LED166.1 (DO), LED167.3 (DI)
unnamed: LED167.1 (DO), LED168.3 (DI)
unnamed: LED168.1 (DO), LED169.3 (DI)
unnamed: LED169.1 (DO), LED170.3 (DI)
unnamed: LED170.1 (DO), LED171.3 (DI)
unnamed: LED171.1 (DO), LED172.3 (DI)
unnamed: LED172.1 (DO), LED173.3 (DI)
unnamed: LED173.1 (DO), LED174.3 (DI)
unnamed: LED174.1 (DO), LED175.3 (DI)
unnamed: LED175.1 (DO), LED176.3 (DI)
unnamed: LED177.1 (DO), LED178.3 (DI)
unnamed: LED178.1 (DO), LED179.3 (DI)
unnamed: LED179.1 (DO), LED180.3 (DI)
unnamed: LED180.1 (DO), LED181.3 (DI)
unnamed: LED181.1 (DO), LED182.3 (DI)
unnamed: LED182.1 (DO), LED183.3 (DI)
unnamed: LED183.1 (DO), LED184.3 (DI)
unnamed: LED184.1 (DO), LED185.3 (DI)
unnamed: LED185.1 (DO), LED186.3 (DI)
unnamed: LED186.1 (DO), LED187.3 (DI)
unnamed: LED187.1 (DO), LED188.3 (DI)
unnamed: LED188.1 (DO), LED189.3 (DI)
unnamed: LED189.1 (DO), LED190.3 (DI)
unnamed: LED190.1 (DO), LED191.3 (DI)
unnamed: LED191.1 (DO), LED192.3 (DI)
unnamed: LED193.1 (DO), LED194.3 (DI)
unnamed: LED194.1 (DO), LED195.3 (DI)
unnamed: LED195.1 (DO), LED196.3 (DI)
unnamed: LED196.1 (DO), LED197.3 (DI)
unnamed: LED197.1 (DO), LED198.3 (DI)
unnamed: LED198.1 (DO), LED199.3 (DI)
unnamed: LED199.1 (DO), LED200.3 (DI)
unnamed: LED200.1 (DO), LED201.3 (DI)
unnamed: LED201.1 (DO), LED202.3 (DI)
unnamed: LED202.1 (DO), LED203.3 (DI)
unnamed: LED203.1 (DO), LED204.3 (DI)
unnamed: LED204.1 (DO), LED205.3 (DI)
unnamed: LED205.1 (DO), LED206.3 (DI)
unnamed: LED206.1 (DO), LED207.3 (DI)
unnamed: LED207.1 (DO), LED208.3 (DI)
unnamed: LED209.1 (DO), LED210.3 (DI)
unnamed: LED210.1 (DO), LED211.3 (DI)
unnamed: LED211.1 (DO), LED212.3 (DI)
unnamed: LED212.1 (DO), LED213.3 (DI)
unnamed: LED213.1 (DO), LED214.3 (DI)
unnamed: LED214.1 (DO), LED215.3 (DI)
unnamed: LED215.1 (DO), LED216.3 (DI)
unnamed: LED216.1 (DO), LED217.3 (DI)
unnamed: LED217.1 (DO), LED218.3 (DI)
unnamed: LED218.1 (DO), LED219.3 (DI)
unnamed: LED219.1 (DO), LED220.3 (DI)
unnamed: LED220.1 (DO), LED221.3 (DI)
unnamed: LED221.1 (DO), LED222.3 (DI)
unnamed: LED222.1 (DO), LED223.3 (DI)
unnamed: LED223.1 (DO), LED224.3 (DI)
unnamed: LED225.1 (DO), LED226.3 (DI)
unnamed: LED226.1 (DO), LED227.3 (DI)
unnamed: LED227.1 (DO), LED228.3 (DI)
unnamed: LED228.1 (DO), LED229.3 (DI)
unnamed: LED229.1 (DO), LED230.3 (DI)
unnamed: LED230.1 (DO), LED231.3 (DI)
unnamed: LED231.1 (DO), LED232.3 (DI)
unnamed: LED232.1 (DO), LED233.3 (DI)
unnamed: LED233.1 (DO), LED234.3 (DI)
unnamed: LED234.1 (DO), LED235.3 (DI)
unnamed: LED235.1 (DO), LED236.3 (DI)
unnamed: LED236.1 (DO), LED237.3 (DI)
unnamed: LED237.1 (DO), LED238.3 (DI)
unnamed: LED238.1 (DO), LED239.3 (DI)
unnamed: LED239.1 (DO), LED240.3 (DI)
unnamed: LED241.1 (DO), LED242.3 (DI)
unnamed: LED242.1 (DO), LED243.3 (DI)
unnamed: LED243.1 (DO), LED244.3 (DI)
unnamed: LED244.1 (DO), LED245.3 (DI)
unnamed: LED245.1 (DO), LED246.3 (DI)
unnamed: LED246.1 (DO), LED247.3 (DI)
unnamed: LED247.1 (DO), LED248.3 (DI)
unnamed: LED248.1 (DO), LED249.3 (DI)
unnamed: LED249.1 (DO), LED250.3 (DI)
unnamed: LED250.1 (DO), LED251.3 (DI)
unnamed: LED251.1 (DO), LED252.3 (DI)
unnamed: LED252.1 (DO), LED253.3 (DI)
unnamed: LED253.1 (DO), LED254.3 (DI)
unnamed: LED254.1 (DO), LED255.3 (DI)
unnamed: LED255.1 (DO), LED256.3 (DI)

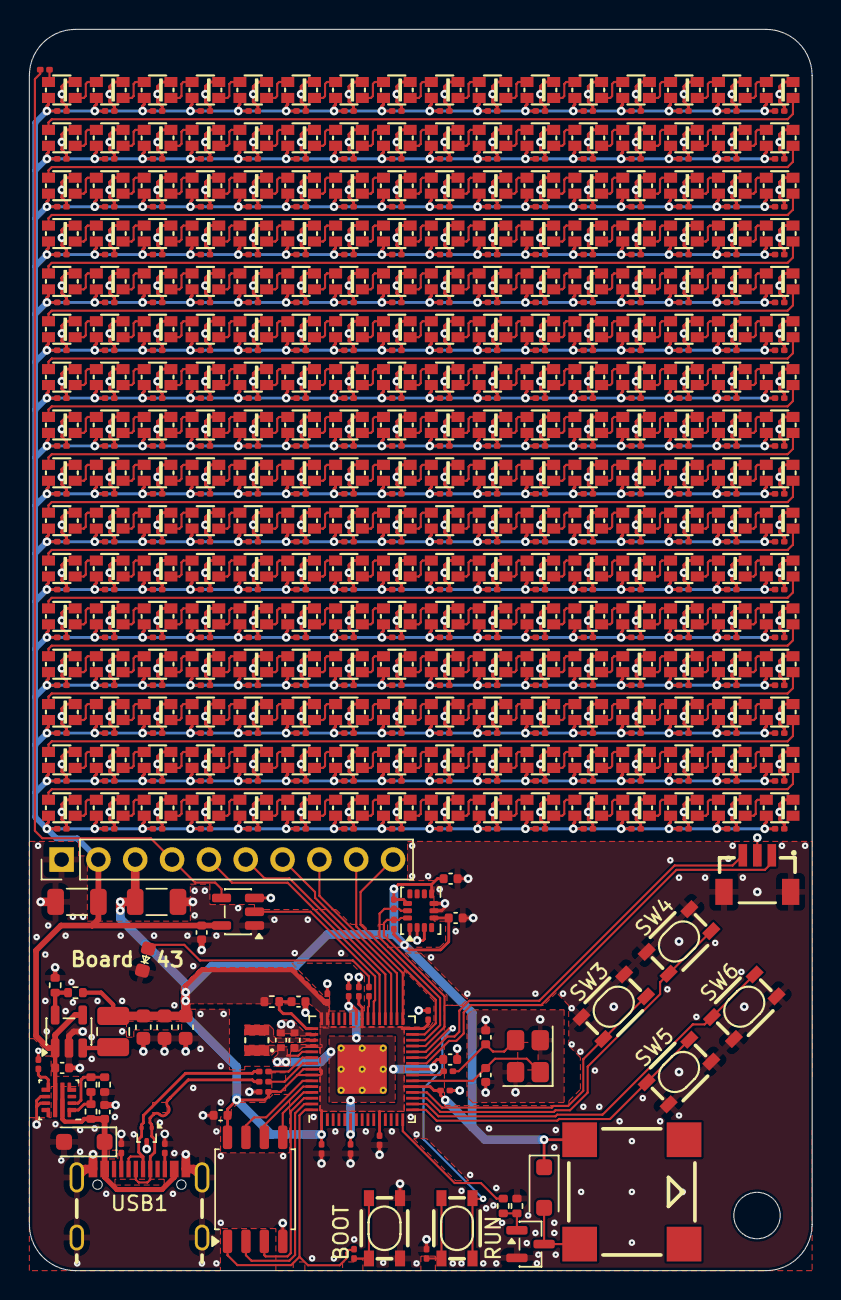
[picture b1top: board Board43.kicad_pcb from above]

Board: 2 copper layers, 54.0 x 85.6 mm, 583 parts (0 on the bottom side), 307 nets.

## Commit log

2026-04-21 hello world
2026-04-21 docs: add LICENSE for the firmware
2026-04-22 refactor: add PCB licenses
    Rename symbol and footprint libraries from Board43 to Board43_KiCad
    to clarify they are project-specific KiCad libraries. Update library
    tables, schematic, and PCB references accordingly.
    Add CERN-OHL-W-2.0 and CC-BY-SA-4.0 license files for the PCB design.
2026-04-22 docs: add project overview and directory structure to README
2026-04-22 docs: add Japanese screenshots
2026-04-22 docs: add Rotate for the animation type
2026-04-22 add scroll_two_patterns_right
2026-04-22 add scroll_two_patterns_with_switch
2026-04-23 feat: add board43-image-transformer crate
    Provides a Rust library, CLI, and WASM module that converts arbitrary
    images into 16×16 RGB data for Board43's WS2812 LED matrix, with
    letterboxing to preserve aspect ratio and gamma correction for LED
    output.
2026-04-23 docs: clarify image upload uses board43-image-transformer WASM
2026-04-24 Fix GitHub link in README_en.md
    Updated GitHub link to point to the correct path for examples.
